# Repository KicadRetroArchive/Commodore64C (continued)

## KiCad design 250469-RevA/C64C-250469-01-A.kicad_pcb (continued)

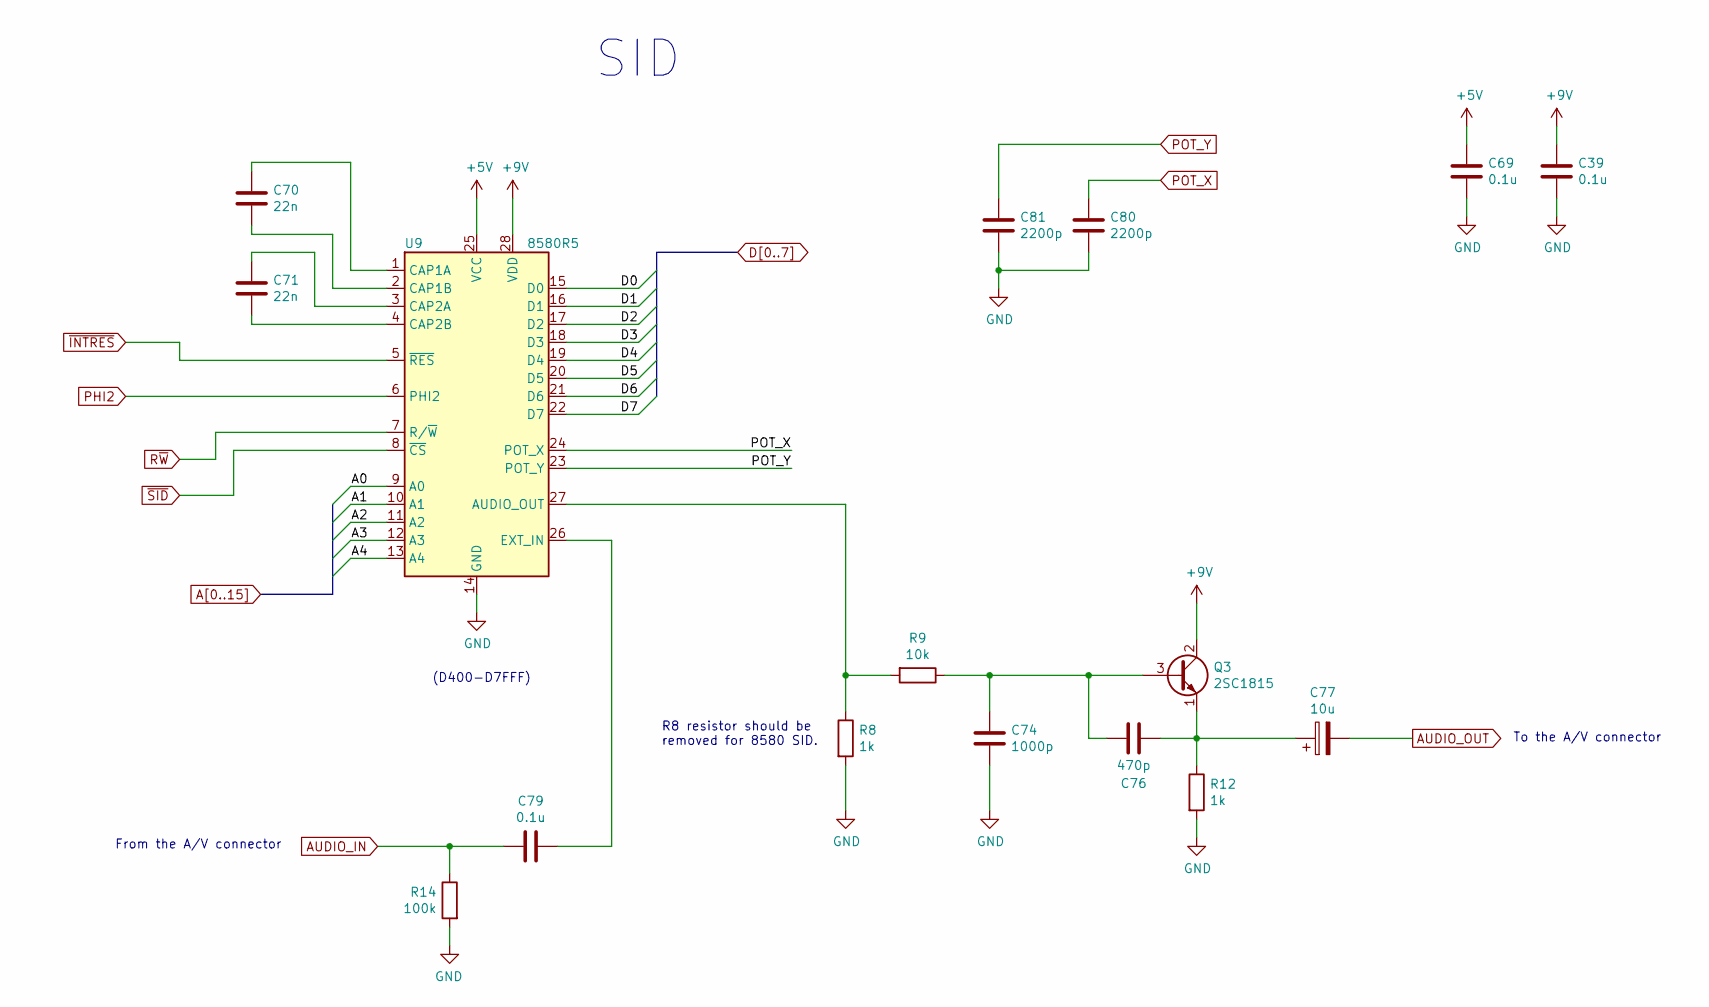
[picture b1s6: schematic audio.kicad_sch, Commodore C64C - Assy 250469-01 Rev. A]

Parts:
C39, C69, C79: 0.1u; C_Disc_D4.7mm_W2.5mm_P5.00mm
C70, C71: 22n; C_Disc_D4.7mm_W2.5mm_P5.00mm
C74: 1000p; C_Disc_D4.7mm_W2.5mm_P5.00mm
C76: 470p; C_Disc_D4.7mm_W2.5mm_P5.00mm
C77: 10u; CP_Radial_D10.0mm_P5.00mm
C80, C81: 2200p; C_Disc_D4.7mm_W2.5mm_P5.00mm
Q3: 2SC1815; TO-92_Inline
R8, R12: 1k; R_Axial_DIN0207_L6.3mm_D2.5mm_P5.08mm_Vertical
R9: 10k; R_Axial_DIN0207_L6.3mm_D2.5mm_P5.08mm_Vertical
R14: 100k; R_Axial_DIN0207_L6.3mm_D2.5mm_P5.08mm_Vertical
U9: 8580R5; DIP-28_W15.24mm_Socket

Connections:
+5V: C69.1, U9.25 (VCC); also elsewhere on the board
+9V: C39.1, Q3.2 (C), U9.28 (VDD); also elsewhere on the board
A0: U9.9 (A0); also elsewhere on the board
A1: U9.10 (A1); also elsewhere on the board
A2: U9.11 (A2); also elsewhere on the board
A3: U9.12 (A3); also elsewhere on the board
A4: U9.13 (A4); also elsewhere on the board
AUDIO_IN: C79.1, R14.1; also elsewhere on the board
AUDIO_OUT: C77.2; also elsewhere on the board
D0: U9.15 (D0); also elsewhere on the board
D1: U9.16 (D1); also elsewhere on the board
D2: U9.17 (D2); also elsewhere on the board
D3: U9.18 (D3); also elsewhere on the board
D4: U9.19 (D4); also elsewhere on the board
D5: U9.20 (D5); also elsewhere on the board
D6: U9.21 (D6); also elsewhere on the board
D7: U9.22 (D7); also elsewhere on the board
GND: C39.2, C69.2, C74.2, C80.2, C81.2, R8.2, R12.2, R14.2, U9.14 (GND); also elsewhere on the board
unnamed: C70.1, U9.1 (CAP1A)
unnamed: C70.2, U9.2 (CAP1B)
unnamed: C71.1, U9.3 (CAP2A)
unnamed: C71.2, U9.4 (CAP2B)
unnamed: C74.1, C76.1, Q3.3 (B), R9.1
unnamed: C76.2, C77.1, Q3.1 (E), R12.1
unnamed: C79.2, U9.26 (EXT_IN)
unnamed: R8.1, R9.2, U9.27 (AUDIO_OUT)
PHI2: U9.6 (PHI2); also elsewhere on the board
POT_X: C80.1, U9.24 (POT_X); also elsewhere on the board
POT_Y: C81.1, U9.23 (POT_Y); also elsewhere on the board
R~W: U9.7 (R/~W); also elsewhere on the board
~INTRES: U9.5 (~RES); also elsewhere on the board
~SID: U9.8 (~CS); also elsewhere on the board

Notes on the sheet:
R8 resistor should be removed for 8580 SID.
To the A/V connector
SID
(D400-D7FFF)
From the A/V connector

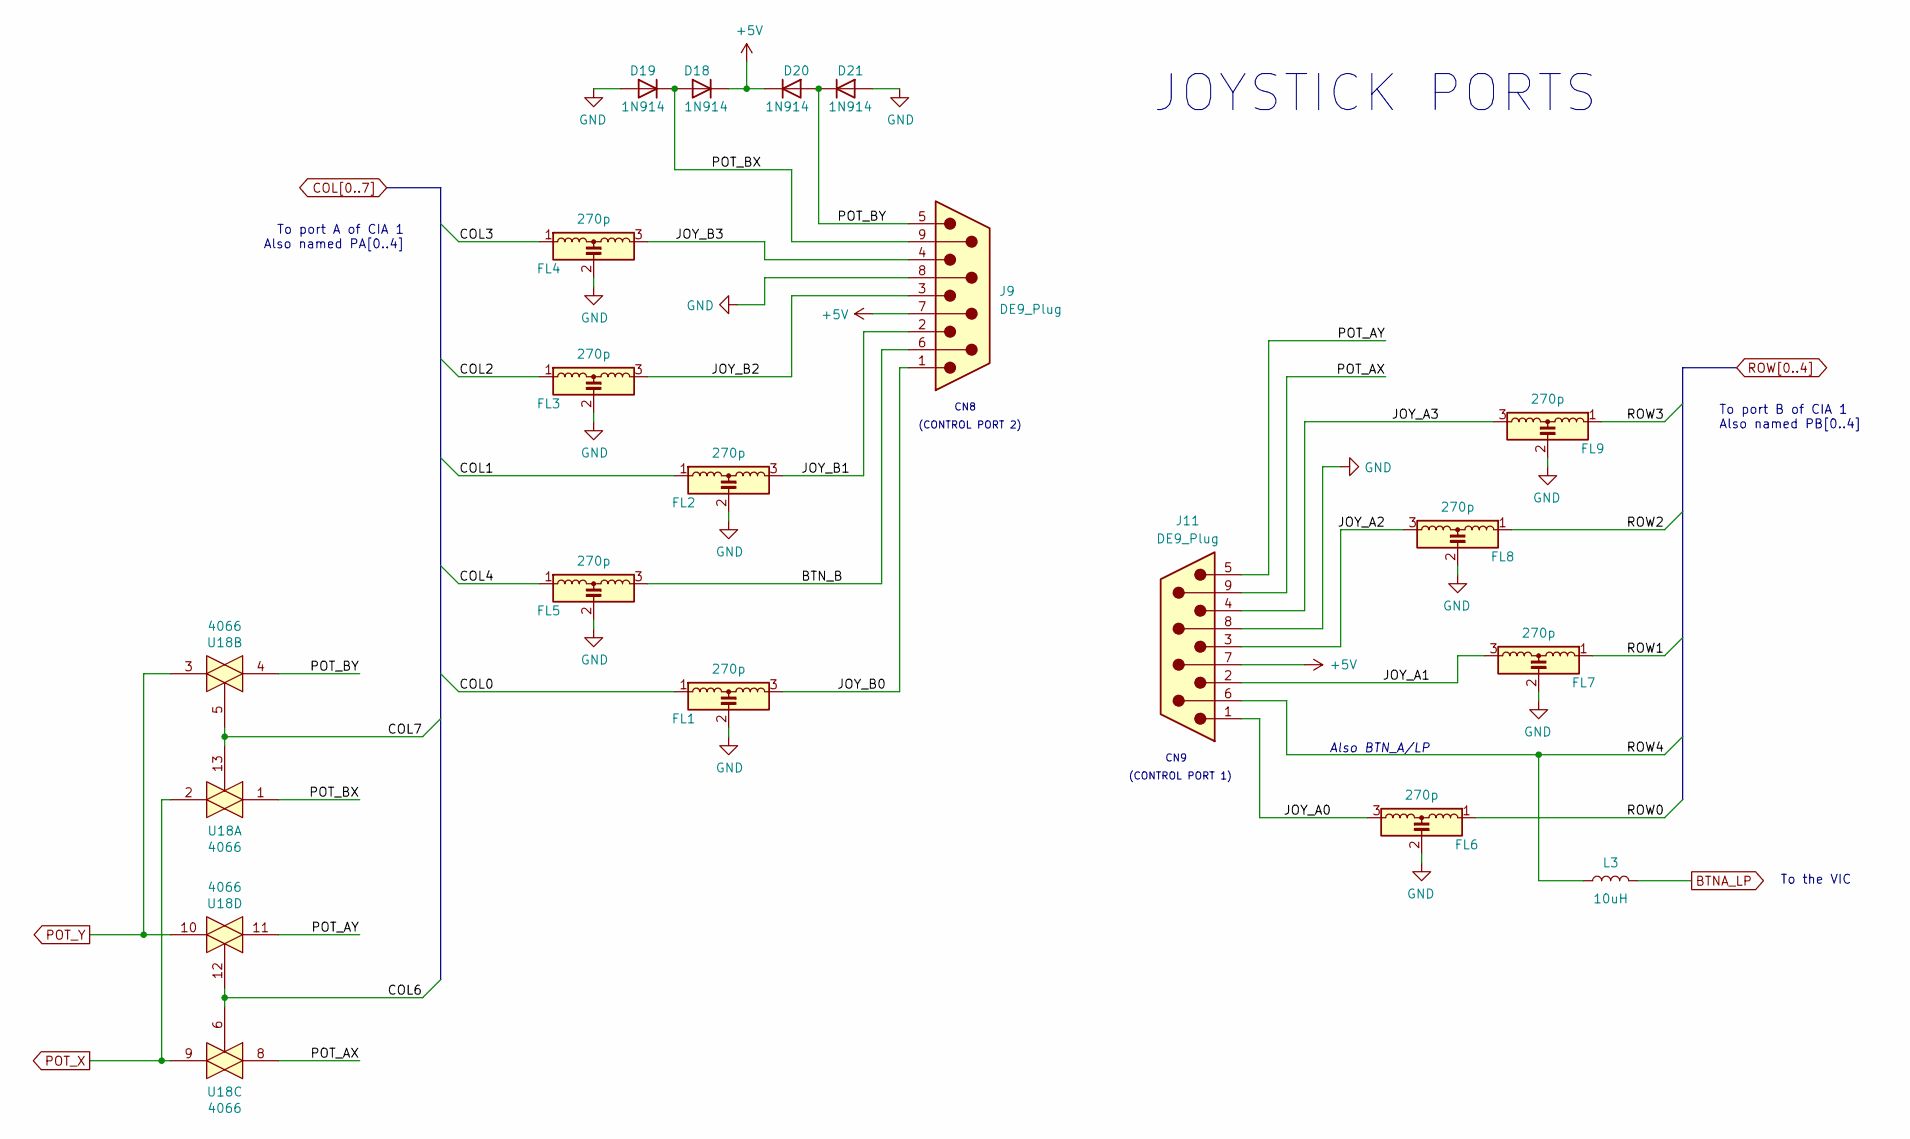
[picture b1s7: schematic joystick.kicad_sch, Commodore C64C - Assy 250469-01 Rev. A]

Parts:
D18, D19, D20, D21: 1N914; D_DO-35_SOD27_P7.62mm_Horizontal
FL1, FL2, FL3, FL4, FL5, FL6, FL7, FL8, FL9: 270p; LCL-Filter_2.8x8.5mm_P2.5mm
J9, J11: DE9_Plug
L3: 10uH; L_Radial_L7.5mm_W3mm_P5.00mm_Kemet_SBT-02
U18: 4066; DIP-14_W7.62mm_Socket

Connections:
+5V: D18.1 (K), D20.1 (K), J9.7, J11.7; also elsewhere on the board
BTNA_LP: L3.1; also elsewhere on the board
COL0: FL1.1; also elsewhere on the board
COL1: FL2.1; also elsewhere on the board
COL2: FL3.1; also elsewhere on the board
COL3: FL4.1; also elsewhere on the board
COL4: FL5.1; also elsewhere on the board
COL6: U18.6, U18.12; also elsewhere on the board
COL7: U18.5, U18.13; also elsewhere on the board
GND: D19.2 (A), D21.2 (A), FL1.2, FL2.2, FL3.2, FL4.2, FL5.2, FL6.2, FL7.2, FL8.2, FL9.2, J9.8, J11.8; also elsewhere on the board
POT_X: U18.2, U18.9; also elsewhere on the board
POT_Y: U18.3, U18.10; also elsewhere on the board
ROW0: FL6.1; also elsewhere on the board
ROW1: FL7.1; also elsewhere on the board
ROW2: FL8.1; also elsewhere on the board
ROW3: FL9.1; also elsewhere on the board

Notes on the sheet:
(CONTROL PORT 1)
(CONTROL PORT 2)
CN8
Also BTN_A/LP
To port B of CIA 1 Also named PB[0..4]
JOYSTICK PORTS
To port A of CIA 1 Also named PA[0..4]
CN9
To the VIC

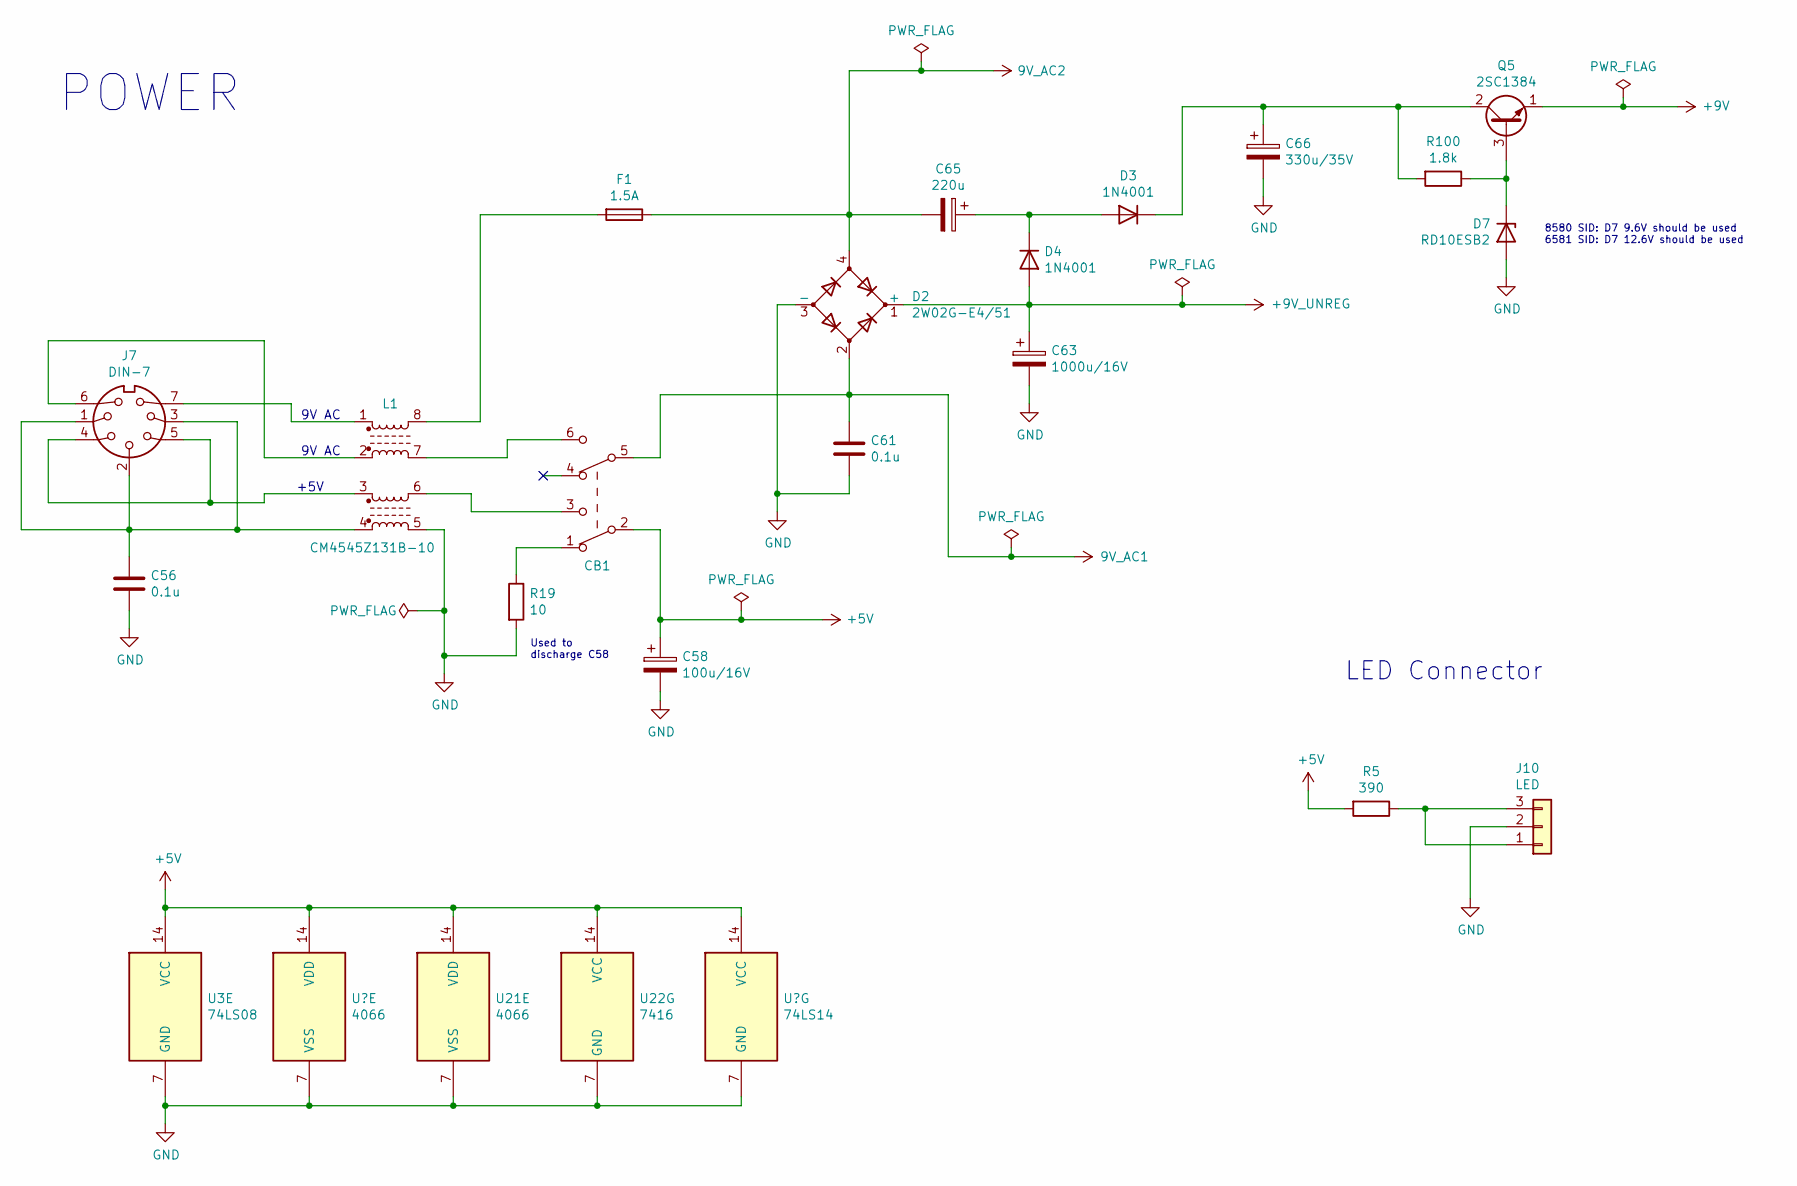
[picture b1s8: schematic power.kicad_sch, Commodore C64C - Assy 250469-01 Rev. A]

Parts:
C56, C61: 0.1u; C_Disc_D4.7mm_W2.5mm_P5.00mm
C58: 100u/16V; CP_Radial_D10.0mm_P5.00mm
C63: 1000u/16V; CP_Axial_L30.0mm_D15.0mm_P35.00mm_Horizontal
C65: 220u; CP_Radial_D10.0mm_P5.00mm
C66: 330u/35V; CP_Radial_D12.5mm_P5.00mm
CB1: SW_DPDT; RockerSwitch_CuK_DPDT_E201J1AV2
D2: 2W02G-E4/51; Diode_Bridge_Round_D9.8mm
D3, D4: 1N4001; D_DO-41_SOD81_P10.16mm_Horizontal
D7: RD10ESB2; D_DO-34_SOD68_P7.62mm_Horizontal
F1: 1.5A; Fuseclip_Cylinder-6.3x32mm
J7: DIN-7; C64_Original_DIN-7_Circular
J10: LED; PinHeader_1x03_P2.54mm_Vertical
L1: CM4545Z131B-10; Laird_CM4545Z131B-10
Q5: 2SC1384; TO-92L_Inline
R5: 390; R_Axial_DIN0207_L6.3mm_D2.5mm_P5.08mm_Vertical
R19: 10; R_Axial_DIN0309_L9.0mm_D3.2mm_P15.24mm_Horizontal
R100: 1.8k; R_Axial_DIN0207_L6.3mm_D2.5mm_P5.08mm_Vertical
U3: 74LS08; DIP-14_W7.62mm_Socket
U18, U21: 4066; DIP-14_W7.62mm_Socket
U22: 7416; DIP-14_W7.62mm_Socket
U23: 74LS14; DIP-14_W7.62mm_Socket

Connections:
9V_AC1: C61.1, CB1.5 (B), D2.2; also elsewhere on the board
9V_AC2: C65.2, D2.4, F1.1; also elsewhere on the board
+5V: C58.1, CB1.2 (B), R5.2, U3.14 (VCC), U18.14 (VDD), U21.14 (VDD), U22.14 (VCC), U23.14 (VCC); also elsewhere on the board
+9V: Q5.1 (E); also elsewhere on the board
+9V_UNREG: C63.1, D2.1 (+), D4.2 (A); also elsewhere on the board
GND: C56.2, C58.2, C61.2, C63.2, C66.2, D2.3 (-), D7.2 (A), J7.0, J10.2, L1.5, R19.2, U3.7 (GND), U18.7 (VSS), U21.7 (VSS), U22.7 (GND), U23.7 (GND); also elsewhere on the board
unnamed: C56.1, J7.1, J7.2, J7.3, L1.4
unnamed: C65.1, D3.2 (A), D4.1 (K)
unnamed: C66.1, D3.1 (K), Q5.2 (C), R100.2
unnamed: CB1.1 (A), R19.1
unnamed: CB1.3 (C), L1.6
unnamed: CB1.6 (C), L1.7
unnamed: D7.1 (K), Q5.3 (B), R100.1
unnamed: F1.2, L1.8
unnamed: J7.4, J7.5, L1.3
unnamed: J7.6, L1.2
unnamed: J7.7, L1.1
unnamed: J10.1, J10.3, R5.1

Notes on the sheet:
+5V
POWER
LED Connector
8580 SID: D7 9.6V should be used 6581 SID: D7 12.6V should be used
Used to discharge C58
9V AC

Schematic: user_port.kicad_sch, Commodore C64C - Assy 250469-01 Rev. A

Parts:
C6, C90: 470p; C_Disc_D4.7mm_W2.5mm_P5.00mm
C28, C29, C30: 0.1u; C_Disc_D4.7mm_W2.5mm_P5.00mm
C43: 220u; CP_Radial_D8.0mm_P5.00mm
C86, C87, C88: 220p; C_Disc_D4.7mm_W2.5mm_P5.00mm
D5: 1N914; D_DO-35_SOD27_P7.62mm_Horizontal
J2: Conn_02x12_Edge; Connector_Edge_2x12_P3.96mm
RN3: 3.3k; R_Array_SIP8
RN6: 1k; R_Array_SIP6
U2: 6526A; DIP-40_W15.24mm_Socket
U22: 7416; DIP-14_W7.62mm_Socket
U23: 74LS14; DIP-14_W7.62mm_Socket

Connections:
9V_AC1: C28.1, J2.10; also elsewhere on the board
9V_AC2: C29.1, J2.11; also elsewhere on the board
+5V: C30.1, D5.1 (K), J2.2, RN3.1 (common), RN6.1 (common), U2.20 (VCC); also elsewhere on the board
/User Port - CIA 2/ATNOUT: U2.5 (PA3), U22.9
/User Port - CIA 2/CLKOUT: U2.6 (PA4), U22.3
/User Port - CIA 2/CNT2: J2.6, RN3.7 (R6), U2.40 (CNT)
/User Port - CIA 2/DATAOUT: U2.7 (PA5), U22.13
/User Port - CIA 2/PA2: J2.M, U2.4 (PA2)
/User Port - CIA 2/PB0: J2.C, U2.10 (PB0)
/User Port - CIA 2/PB1: J2.D, U2.11 (PB1)
/User Port - CIA 2/PB2: J2.E, U2.12 (PB2)
/User Port - CIA 2/PB3: J2.F, U2.13 (PB3)
/User Port - CIA 2/PB4: J2.H, U2.14 (PB4)
/User Port - CIA 2/PB5: J2.J, U2.15 (PB5)
/User Port - CIA 2/PB6: J2.K, U2.16 (PB6)
/User Port - CIA 2/PB7: J2.L, U2.17 (PB7)
/User Port - CIA 2/SP2: J2.7, RN3.8 (R7), U2.39 (SP)
/User Port - CIA 2/~FLAG_2: C6.1, J2.B, RN3.4 (R3), U2.24 (~FLAG)
/User Port - CIA 2/~PC2: J2.8, U2.18 (~PC)
A0: U2.38 (RS0); also elsewhere on the board
A1: U2.37 (RS1); also elsewhere on the board
A2: U2.36 (RS2); also elsewhere on the board
A3: U2.35 (RS3); also elsewhere on the board
ATN: C88.1, J2.9, RN6.2 (R1), U22.8; also elsewhere on the board
CLK: RN6.6 (R5), U2.8 (PA6), U22.4; also elsewhere on the board
CNT1: C86.1, J2.4, RN3.5 (R4); also elsewhere on the board
D0: U2.33 (DB0); also elsewhere on the board
D1: U2.32 (DB1); also elsewhere on the board
D2: U2.31 (DB2); also elsewhere on the board
D3: U2.30 (DB3); also elsewhere on the board
D4: U2.29 (DB4); also elsewhere on the board
D5: U2.28 (DB5); also elsewhere on the board
D6: U2.27 (DB6); also elsewhere on the board
D7: U2.26 (DB7); also elsewhere on the board
DATA: RN6.4 (R3), U2.9 (PA7), U22.12; also elsewhere on the board
GND: C6.2, C28.2, C29.2, C30.2, C43.2, C86.2, C87.2, C88.2, C90.2, J2.1, J2.12, J2.A, J2.N, U2.1 (GND); also elsewhere on the board
unnamed: C43.1, D5.2 (A), RN3.3 (R2), U23.5
unnamed: U22.1, U22.5, U23.6
PHI2: U2.25 (PHI2); also elsewhere on the board
R~W: U2.22 (R/W); also elsewhere on the board
SP1: C87.1, J2.5, RN3.6 (R5); also elsewhere on the board
TOD: U2.19 (TOD); also elsewhere on the board
~CIA2: U2.23 (~CS); also elsewhere on the board
~EXTRST: RN6.5 (R4), U22.6; also elsewhere on the board
~INTRES: C90.1, J2.3, RN6.3 (R2), U2.34 (~RES), U22.2; also elsewhere on the board
~NMI: RN3.2 (R1), U2.21 (~IRQ); also elsewhere on the board
~VA14: U2.2 (PA0); also elsewhere on the board
~VA15: U2.3 (PA1); also elsewhere on the board

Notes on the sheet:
(DD00-DDFF)
To Serial Port
USER PORT
From Memory Controller 251715-01
Shared with CIA 1
From Exp
CIA 2
CN2
From CPU
(24 PIN MALE EDGE)
To Serial Port
Low 4 bits of the CPU's address bus
To Memory Controller 251715-01

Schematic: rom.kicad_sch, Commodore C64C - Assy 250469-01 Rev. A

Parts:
U4: 23128; DIP-28_W15.24mm_Socket
U5: 2332; DIP-24_W15.24mm_Socket

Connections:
+5V: U4.27 (CS3), U4.28 (VCC), U5.21 (CS2/~CS2), U5.24 (VCC); also elsewhere on the board
A0: U4.10 (A0), U5.8 (A0); also elsewhere on the board
A1: U4.9 (A1), U5.7 (A1); also elsewhere on the board
A2: U4.8 (A2), U5.6 (A2); also elsewhere on the board
A3: U4.7 (A3), U5.5 (A3); also elsewhere on the board
A4: U4.6 (A4), U5.4 (A4); also elsewhere on the board
A5: U4.5 (A5), U5.3 (A5); also elsewhere on the board
A6: U4.4 (A6), U5.2 (A6); also elsewhere on the board
A7: U4.3 (A7), U5.1 (A7); also elsewhere on the board
A8: U4.25 (A8), U5.23 (A8); also elsewhere on the board
A9: U4.24 (A9), U5.22 (A9); also elsewhere on the board
A10: U4.21 (A10), U5.19 (A10); also elsewhere on the board
A11: U4.23 (A11), U5.18 (A11); also elsewhere on the board
A12: U4.2 (A12); also elsewhere on the board
A14: U4.26 (A13); also elsewhere on the board
D0: U4.11 (D0), U5.9 (D0); also elsewhere on the board
D1: U4.12 (D1), U5.10 (D1); also elsewhere on the board
D2: U4.13 (D2), U5.11 (D2); also elsewhere on the board
D3: U4.15 (D3), U5.13 (D3); also elsewhere on the board
D4: U4.16 (D4), U5.14 (D4); also elsewhere on the board
D5: U4.17 (D5), U5.15 (D5); also elsewhere on the board
D6: U4.18 (D6), U5.16 (D6); also elsewhere on the board
D7: U4.19 (D7), U5.17 (D7); also elsewhere on the board
GND: U4.14 (GND), U4.20 (~CS2), U5.12 (GND); also elsewhere on the board
~CHAROM: U5.20 (CS1/~CS1); also elsewhere on the board
~KBR_CS: U4.22 (~CS1); also elsewhere on the board

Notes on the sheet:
CHARACTER ROM (D000-DFFF)
ROM
Not a typo!
KERNAL & BASIC (E000-FFFF) (A000-BFFF)

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
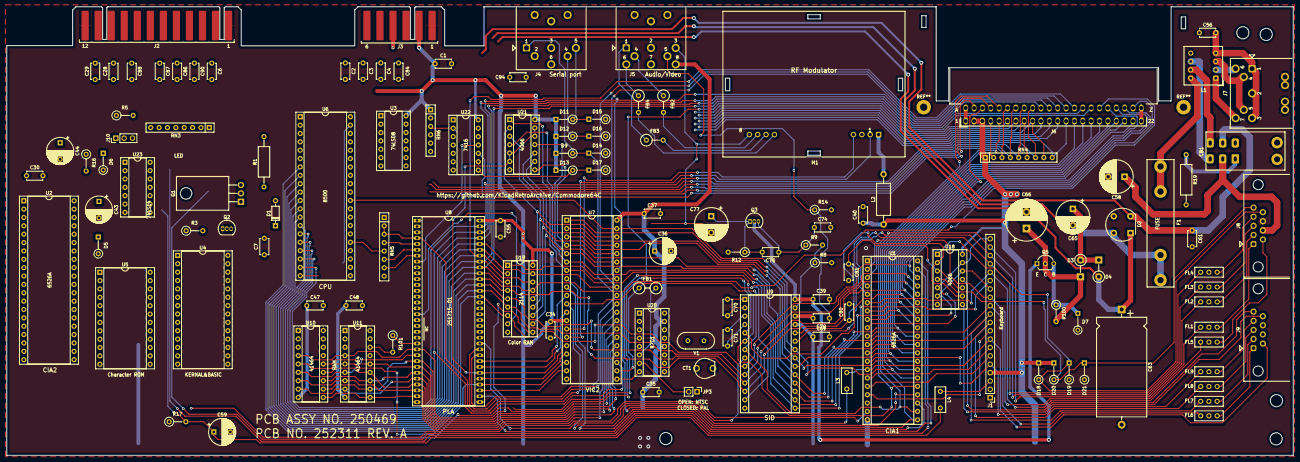
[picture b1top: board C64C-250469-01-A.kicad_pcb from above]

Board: 2 copper layers, 390.6 x 136.2 mm, 131 parts (0 on the bottom side), 187 nets.

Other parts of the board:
J8: DB9_Female; Kycon_K22X-E9P-N_DSUB-9_Male_Horizontal

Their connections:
+5V: J8.7; also elsewhere on the board
GND: J8.8; also elsewhere on the board

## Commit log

2020-04-18 Add schematics and libraries
2020-04-20 Add Kemet SBT-02 choke coil footprints
2020-04-20 Updates and BOMs
2020-04-26 Improve project libraries
2020-04-26 Add initial PCB with placed components
2020-04-29 Add some artwork to the PCB
2020-05-01 Major work on the documentation
2020-05-01 More work on the documentation
2020-05-01 Fix inline image in 250469-RevA/README.md
2020-05-02 Add PDF version of the schematic
2020-05-02 Improved edge connectors
2020-05-02 More work on the PCB
2020-05-03 Pull changes to the KRL
2020-05-03 Updates to the READMEs
2020-05-07 PCB: Add some more silkscreen labels
2020-05-09 Various improvements and changes to footprints
2020-05-10 Change footprint of PLA to Socket version
2020-05-13 Update PDF of schematic
2020-05-13 Change label in Power section
2020-05-16 Modified the edge connectors after measuring the originals
2020-05-16 Corrected board dimensions and connector placements
    The dimensions are now 100% correct after carefully measuring
    a real board I acquired a few days ago.
2020-05-16 Update Rev. A README
2020-05-17 Placed all mounting holes on the PCB
2020-05-21 Changes after updates in the KRL
2020-05-21 Right side routed
2020-05-23 Fixed RF Modulator footprint and added 3D model
2020-05-25 Make pads of expansion connector thinner
2020-05-25 Routed rightmost side of the board
2020-06-02 More routing around CIA 1
2020-06-14 Changed footprint of DIC connectors and wiring of Color RAM
2020-07-12 Minor changes to the memory sheet
2020-07-12 More routing around the memory controller
2020-09-27 Update schematic after changes in libs
2020-09-27 More routing
2020-09-27 Update Service Manual
2021-11-08 Update README.md
    https://forum.kicad.info/t/warning-avoid-all-links-to-kicad-pcb-org-use-kicad-org/31521
2023-04-02 Initial port to v7
2023-04-11 Footprints and Symbols updates
2023-04-16 Fix DIN-8 Video connector
    Footprint, symbol and conections to modulator
    were all wrong.
2023-04-29 Rename project library (not finished)
2023-05-29 Fixes after renaming the project library
